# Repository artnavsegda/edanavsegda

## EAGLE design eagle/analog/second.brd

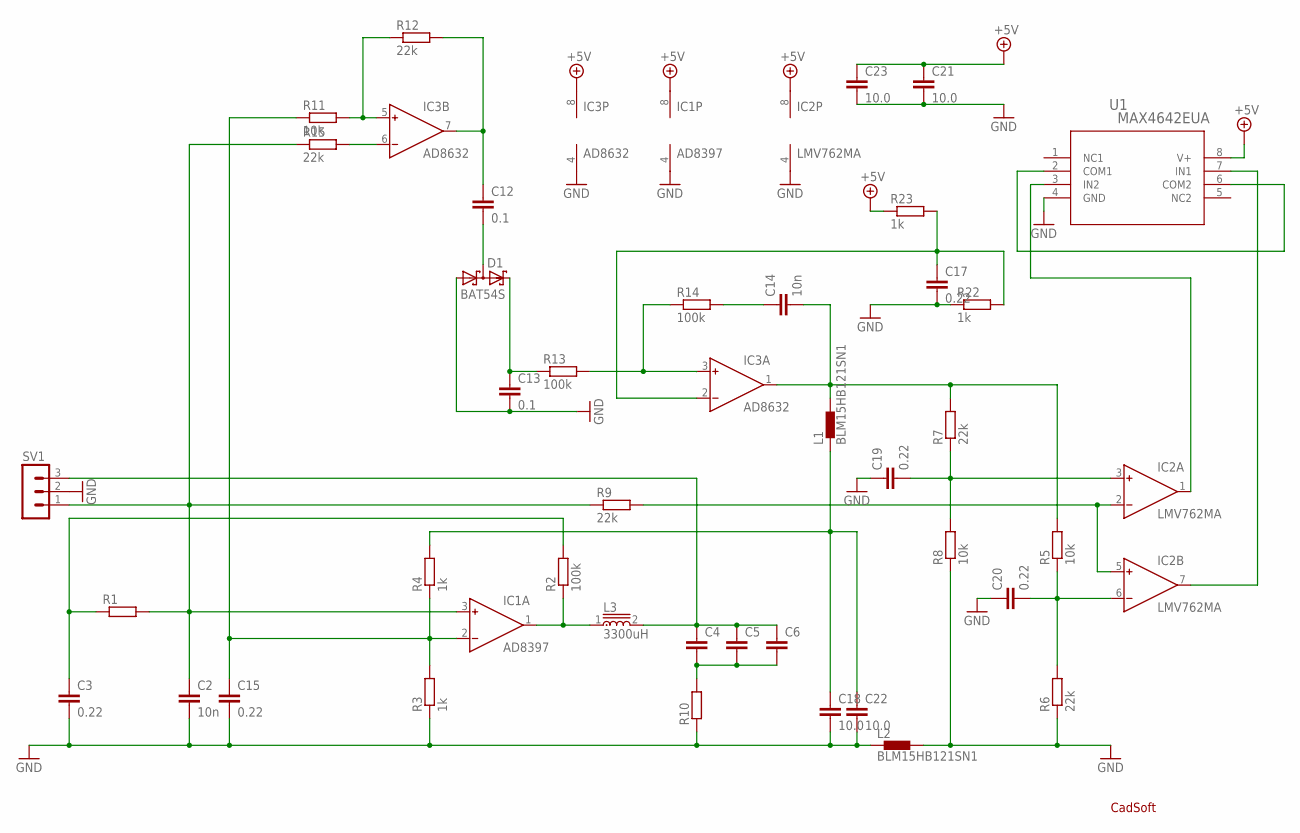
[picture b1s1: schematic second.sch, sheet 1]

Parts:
C2, C14: 10n; C0805
C3, C15, C17, C19, C20: 0.22; C0805
C4, C5, C6: C-EUC0805; C0805
C12, C13: 0.1; C0805
C18, C21, C22, C23: 10.0; C0805
D1: BAT54S; SOT23
IC1: AD8397; SO8
IC2: LMV762MA; SO8
IC3: AD8632; SO8
L1, L2: BLM15HB121SN1; 0402
L3: 3300uH; P0762NL
R1, R10: R-EU_R0805; R0805
R2, R13, R14: 100k; R0805
R3, R4, R22, R23: 1k; R0805
R5, R8, R11: 10k; R0805
R6, R7, R9, R12, R15: 22k; R0805
SV1: MA03-1
U1: MAX4642EUA; 21-0036K

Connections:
+5V: C21.1, C23.1, IC1.8 (V+), IC2.8 (V+), IC3.8 (V+), R23.1, U1.8 (V+); also elsewhere on the board
GND: C2.2, C3.2, C13.2, C15.2, C17.2, C18.2, C19.1, C20.1, C21.2, C22.2, C23.2, D1.1 (A1), IC1.4 (V-), IC2.4 (V-), IC3.4 (V-), L2.1, L2.2, R3.1, R6.1, R8.1, R10.1, R22.1, SV1.2, U1.4 (GND); also elsewhere on the board
unnamed: IC2.1 (OUT), U1.3 (IN2)
unnamed: U1.2 (COM1), U1.6 (COM2)
unnamed: IC2.2 (IN-), IC2.5 (IN+), R9.2
unnamed: C20.2, IC2.6 (IN-), R5.1, R6.2
unnamed: C19.2, IC2.3 (IN+), R7.1, R8.2
unnamed: C14.2, IC3.1 (OUT), L1.2, R5.2, R7.2
unnamed: C18.1, C22.1, L1.1, R4.2
unnamed: IC2.7 (OUT), U1.7 (IN1)
unnamed: C4.2, C5.2, C6.2, R10.2
unnamed: C4.1, C5.1, C6.1, L3.2, SV1.3
unnamed: C14.1, R14.2
unnamed: IC3.3 (IN+), R13.2, R14.1
unnamed: IC1.1 (OUT), L3.1, R2.1
unnamed: C2.1, IC1.3 (IN+), R1.2, R9.1, R15.1, SV1.1
unnamed: C3.1, R1.1, R2.2
unnamed: C13.1, D1.2 (C2), R13.1
unnamed: C12.2, D1.3 (C1A2)
unnamed: C12.1, IC3.7 (OUT), R12.2
unnamed: IC3.5 (IN+), R11.2, R12.1
unnamed: IC3.6 (IN-), R15.2
unnamed: C15.1, IC1.2 (IN-), R3.2, R4.1, R11.1
unnamed: C17.1, IC3.2 (IN-), R22.2, R23.2

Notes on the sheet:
CadSoft

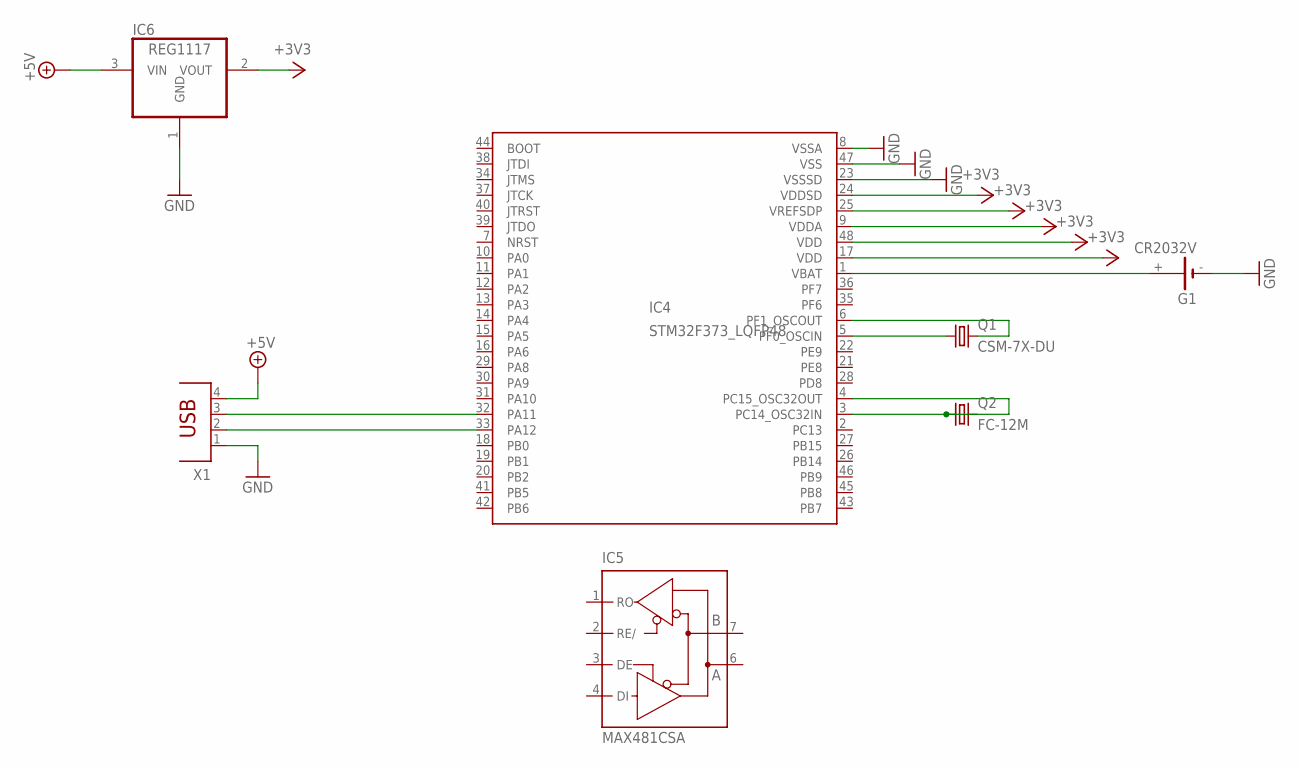
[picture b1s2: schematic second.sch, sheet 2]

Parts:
G1: CR2032V
IC4: STM32F373_LQFP48; LQFP48_PACKAGE
IC5: MAX481CSA; SO08
IC6: REG1117; SOT223
Q1: CSM-7X-DU
Q2: FC-12M
X1: PN61729

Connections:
+3V3: IC4.9 (VDDA), IC4.17 (VDD), IC4.24 (VDDSD), IC4.25 (VREFSDP), IC4.48 (VDD), IC6.2 (VOUT)
+5V: IC6.3 (VIN), X1.4; also elsewhere on the board
GND: G1.-, IC4.8 (VSSA), IC4.23 (VSSSD), IC4.47 (VSS), IC5.5 (GND), IC6.1 (GND), X1.1; also elsewhere on the board
unnamed: G1.+, IC4.1 (VBAT)
unnamed: IC4.5 (PF0_OSCIN), Q1.1
unnamed: IC4.6 (PF1_OSCOUT), Q1.2
unnamed: IC4.3 (PC14_OSC32IN), IC4.4 (PC15_OSC32OUT), Q2.1
unnamed: IC4.32 (PA11), X1.3
unnamed: IC4.33 (PA12), X1.2
VCC: IC5.8 (VCC)

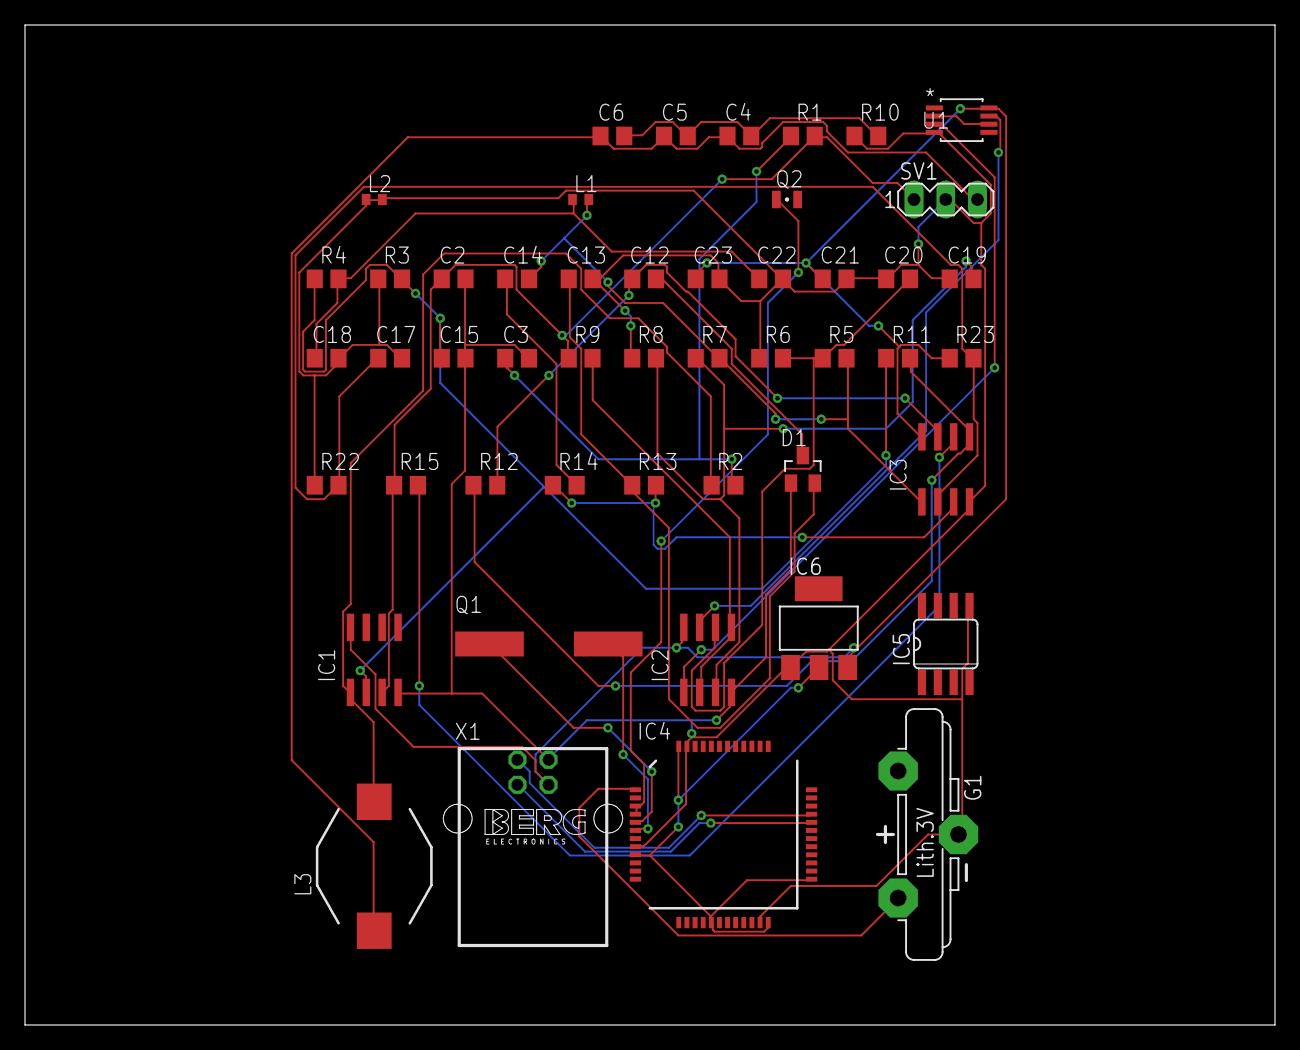
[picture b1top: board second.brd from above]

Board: 2 copper layers, 100.0 x 80.0 mm, 49 parts (0 on the bottom side), 31 nets.

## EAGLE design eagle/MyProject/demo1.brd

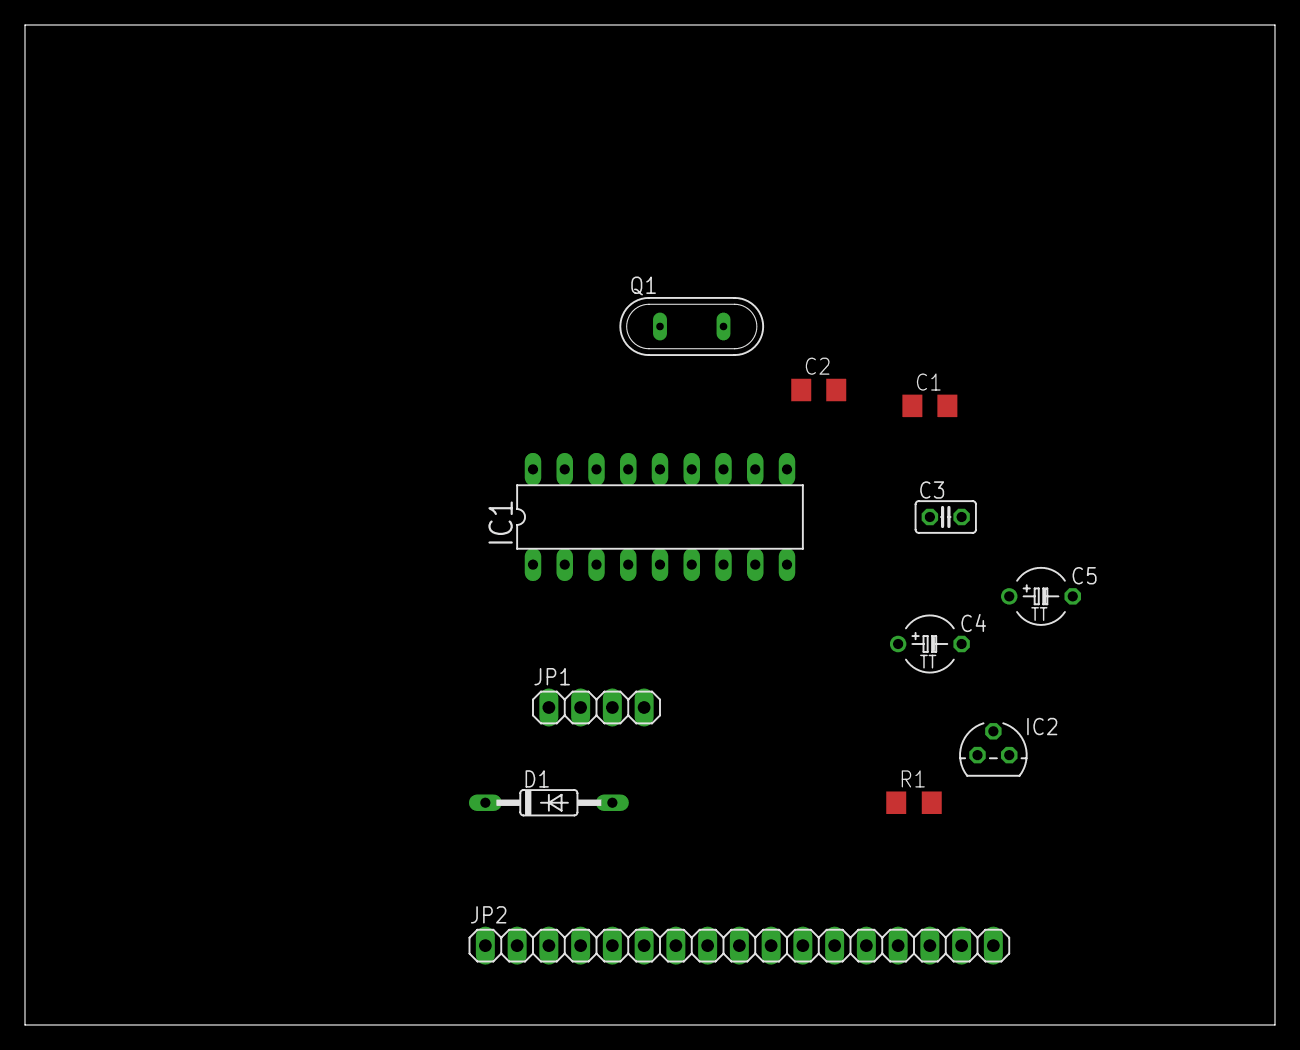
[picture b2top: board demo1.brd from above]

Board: 2 copper layers, 100.0 x 80.0 mm, 12 parts (0 on the bottom side), 21 nets, no tracks yet.

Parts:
C1, C2: 30p; C1206
C3: 10n; C025-025X050
C4: 47u/25V; TAP5-45
C5: 47u; TAP5-45
D1: 1N4148DO35-10; DO35-10
IC1: PIC16F84AP; DIL18
IC2: 78L05Z; TO92
JP1: PROG; 1X04
JP2: APPL; 1X17
Q1: QS
R1: 2,2k; R1206

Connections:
+5V: IC1.14, JP2.15, R1.2
GND: C1.1, C2.1, C3.2, C4.-, C5.-, IC1.5, IC2.2, JP1.4, JP2.17
MCLR/PGM: D1.C, IC1.4, JP1.3, JP2.1
unnamed: C3.1, C4.+, IC2.1
unnamed: C1.2, IC1.16, Q1.2
unnamed: C2.2, IC1.15, Q1.1
unnamed: D1.A, R1.1
RA0: IC1.17, JP2.14
RA1: IC1.18, JP2.13
RA2: IC1.1, JP2.12
RA3: IC1.2, JP2.11
RA4: IC1.3, JP2.10
RB0: IC1.6, JP2.9
RB1: IC1.7, JP2.8
RB2: IC1.8, JP2.7
RB3: IC1.9, JP2.6
RB4: IC1.10, JP2.5
RB5: IC1.11, JP2.4
RB6/CLK: IC1.12, JP1.1, JP2.3
RB7/DATA: IC1.13, JP1.2, JP2.2
V+: C5.+, IC2.3, JP2.16

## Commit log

2017-12-17 getting started doc
2017-12-17 analog
2017-12-17 move
2017-12-17 text
2017-12-17 autoroute
2017-12-17 vdhtdhrth
2017-12-17 podebil
2017-12-20 kicad
2017-12-20 schematic
2017-12-21 pokazhi
2017-12-21 pochemu
2018-02-01 board
2018-02-01 SN74LS86
2018-02-01 memory
2018-02-01 resistor
2018-02-01 govno
2018-02-01 sdsda
2018-02-01 more
2018-02-01 shit
2018-02-01 ssad
2018-02-02 uygfdh
2018-02-02 tajk
2018-02-09 build
2018-04-23 avrisp
2018-04-23 eagle
